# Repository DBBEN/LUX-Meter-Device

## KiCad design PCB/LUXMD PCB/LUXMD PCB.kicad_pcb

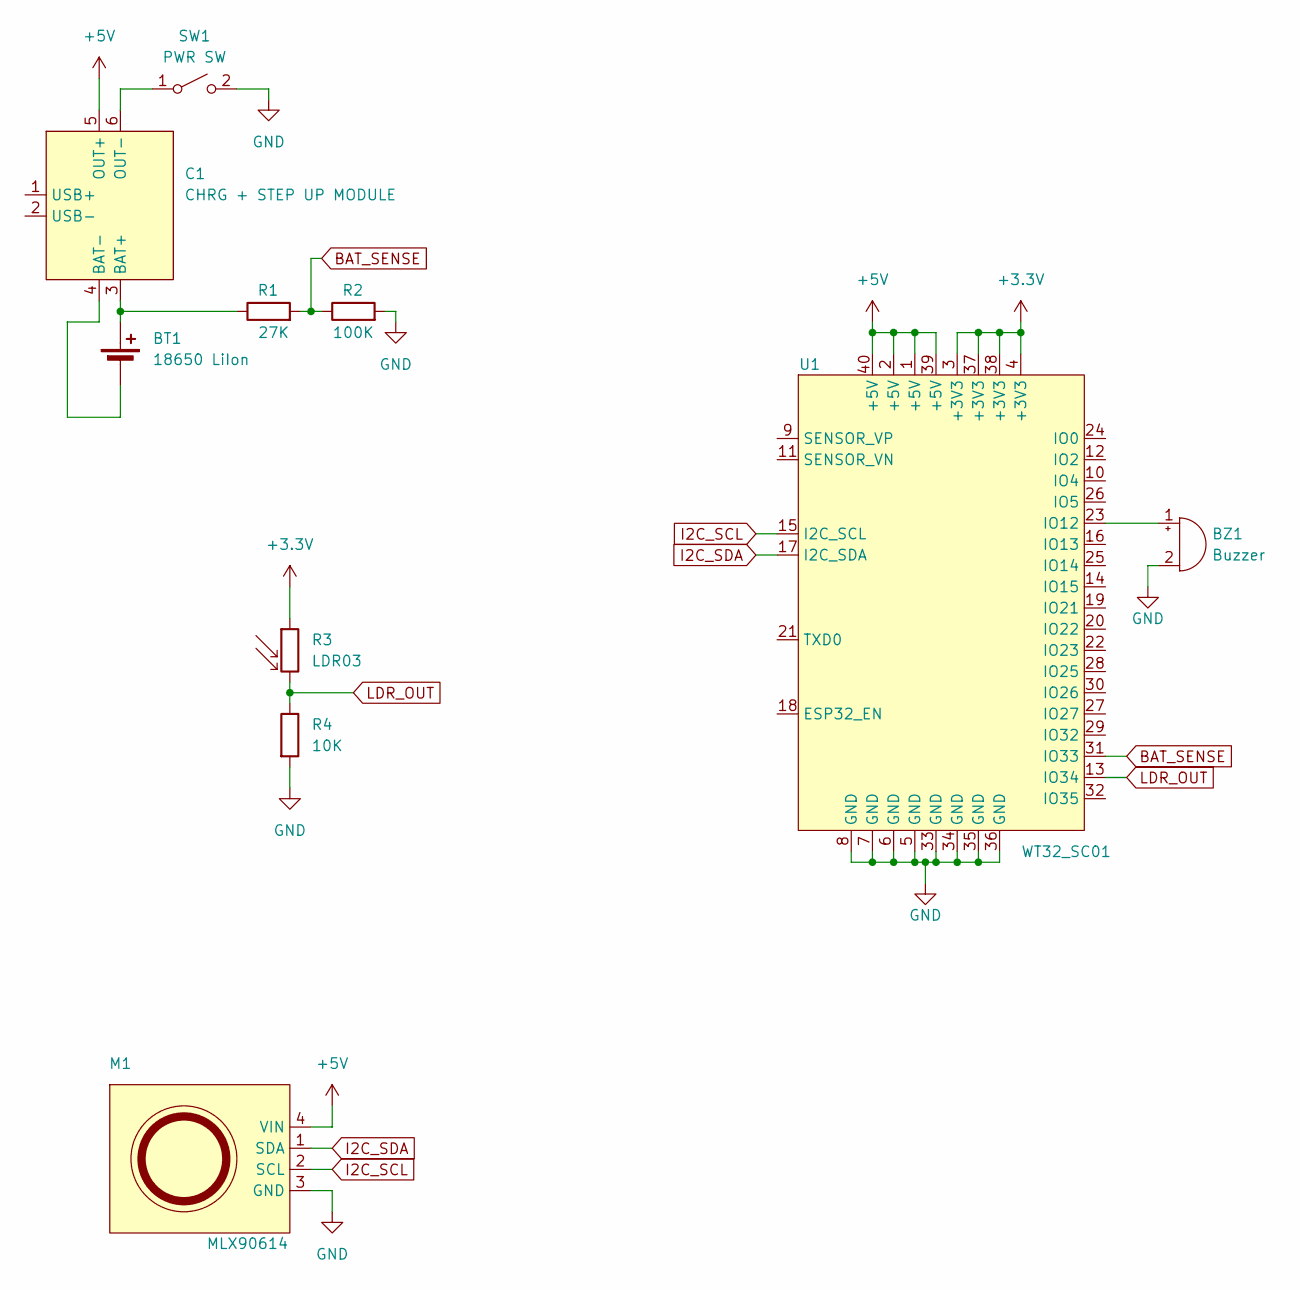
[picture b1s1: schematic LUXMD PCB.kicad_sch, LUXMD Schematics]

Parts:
BT1: 18650 LiIon; JST_EH_B2B-EH-A_1x02_P2.50mm_Vertical
BZ1: Buzzer
C1: CHRG + STEP UP MODULE; TP4056+Step Up Module
M1: MLX90614; JST_EH_B4B-EH-A_1x04_P2.50mm_Vertical
R1: 27K; R_Axial_DIN0207_L6.3mm_D2.5mm_P10.16mm_Horizontal
R2: 100K; R_Axial_DIN0207_L6.3mm_D2.5mm_P10.16mm_Horizontal
R3: LDR03; R_LDR_10x8.5mm_P7.6mm_Vertical
R4: 10K; R_Axial_DIN0207_L6.3mm_D2.5mm_P10.16mm_Horizontal
SW1: PWR SW; JST_EH_B2B-EH-A_1x02_P2.50mm_Vertical
U1: WT32_SC01; PinHeader_2x20_P2.54mm_Vertical

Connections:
+3.3V: R3.1, U1.3 (+3V3), U1.4 (+3V3), U1.37 (+3V3), U1.38 (+3V3)
+5V: C1.5 (OUT+), M1.4 (VIN), U1.1 (+5V), U1.2 (+5V), U1.39 (+5V), U1.40 (+5V)
BAT_SENSE: R1.2, R2.1, U1.31 (IO33)
GND: BZ1.2 (+), M1.3 (GND), R2.2, R4.2, SW1.2 (B), U1.5 (GND), U1.6 (GND), U1.7 (GND), U1.8 (GND), U1.33 (GND), U1.34 (GND), U1.35 (GND), U1.36 (GND)
I2C_SCL: M1.2 (SCL), U1.15 (I2C_SCL)
I2C_SDA: M1.1 (SDA), U1.17 (I2C_SDA)
LDR_OUT: R3.2, R4.1, U1.13 (IO34)
unnamed: BT1.1 (+), C1.3 (BAT+), R1.1
unnamed: BT1.2 (-), C1.4 (BAT-)
unnamed: BZ1.1 (-), U1.23 (IO12)
unnamed: C1.6 (OUT-), SW1.1 (A)

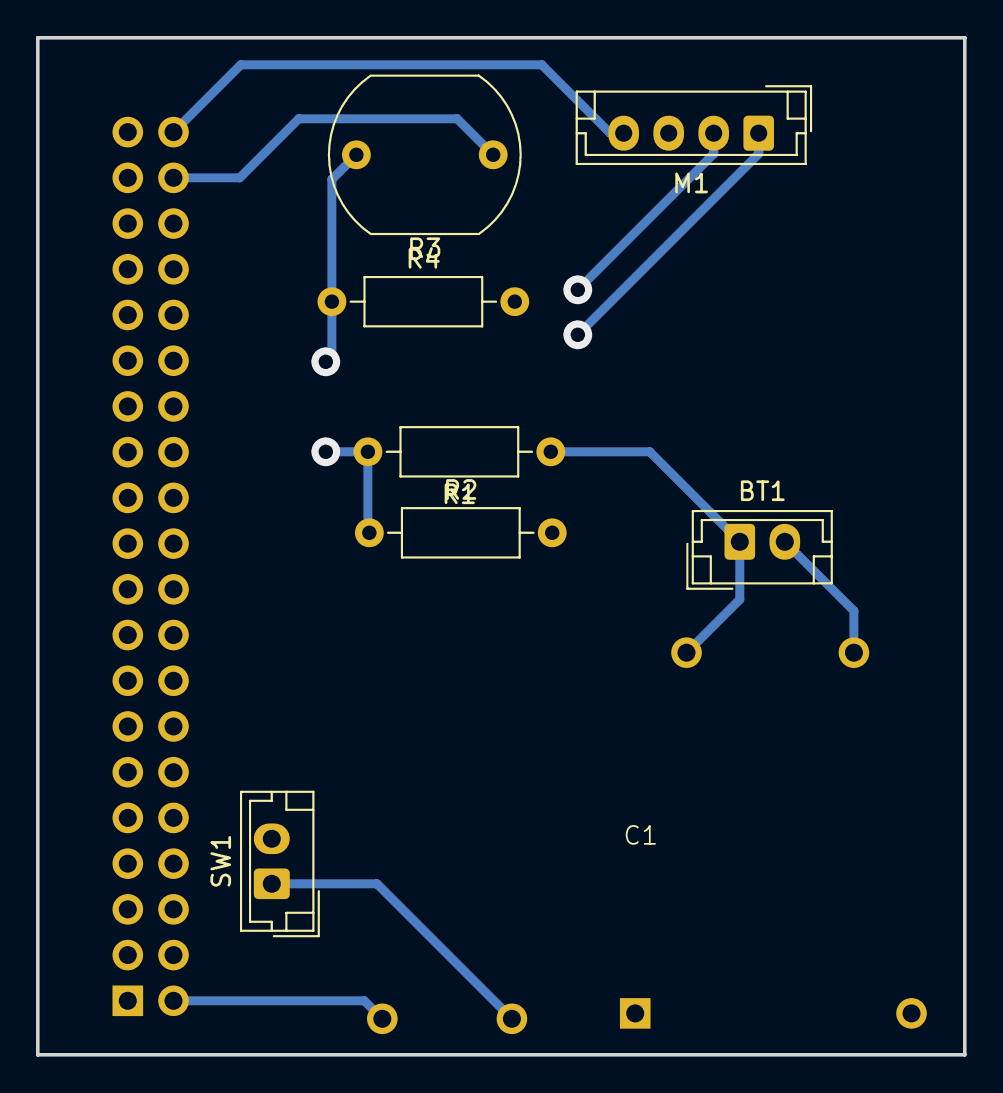
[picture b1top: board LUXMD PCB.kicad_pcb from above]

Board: 2 copper layers, 51.5 x 56.5 mm, 9 parts (1 on the bottom side), 10 nets.

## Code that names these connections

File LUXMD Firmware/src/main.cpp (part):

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#include "addons/RTDBHelper.h"

// PINOUT --------------------------------------------------------------------------------------------------------
#define LDR_OUT_PIN             34
#define BAT_SENSE_PIN           33
#define BUZZER_PIN              12
#define I2C_SDA_PIN             18
#define I2C_SCL_PIN             19             
// ---------------------------------------------------------------------------------------------------------------

// PARAMS --------------------------------------------------------------------------------------------------------
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void setup(void)
{
  Serial.begin(115200);
  I2CMLX.begin(I2C_SDA_PIN, I2C_SCL_PIN);
  display.begin();
  lv_init();

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  lv_timer_handler();

  for(int i = 0; i < BATT_SAMPLES; i++){
    _battPercent += analogRead(BAT_SENSE_PIN);
  }

  _battPercent /= BATT_SAMPLES;
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
    if(!hold){
      _tempOut = mlx.readObjectTempC();
      _ldrOut = analogRead(LDR_OUT_PIN);
      _ldrOut = (m_cal * _ldrOut) + b_cal;
      
      if (_ldrOut < 0) _ldrOut = 0;
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
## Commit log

2025-03-26 lv_conf.h
2025-03-26 lv_conf.h path
